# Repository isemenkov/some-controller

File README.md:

# some-controller

Some controller it is a test project to create simple input-output board with main power supply +24V.

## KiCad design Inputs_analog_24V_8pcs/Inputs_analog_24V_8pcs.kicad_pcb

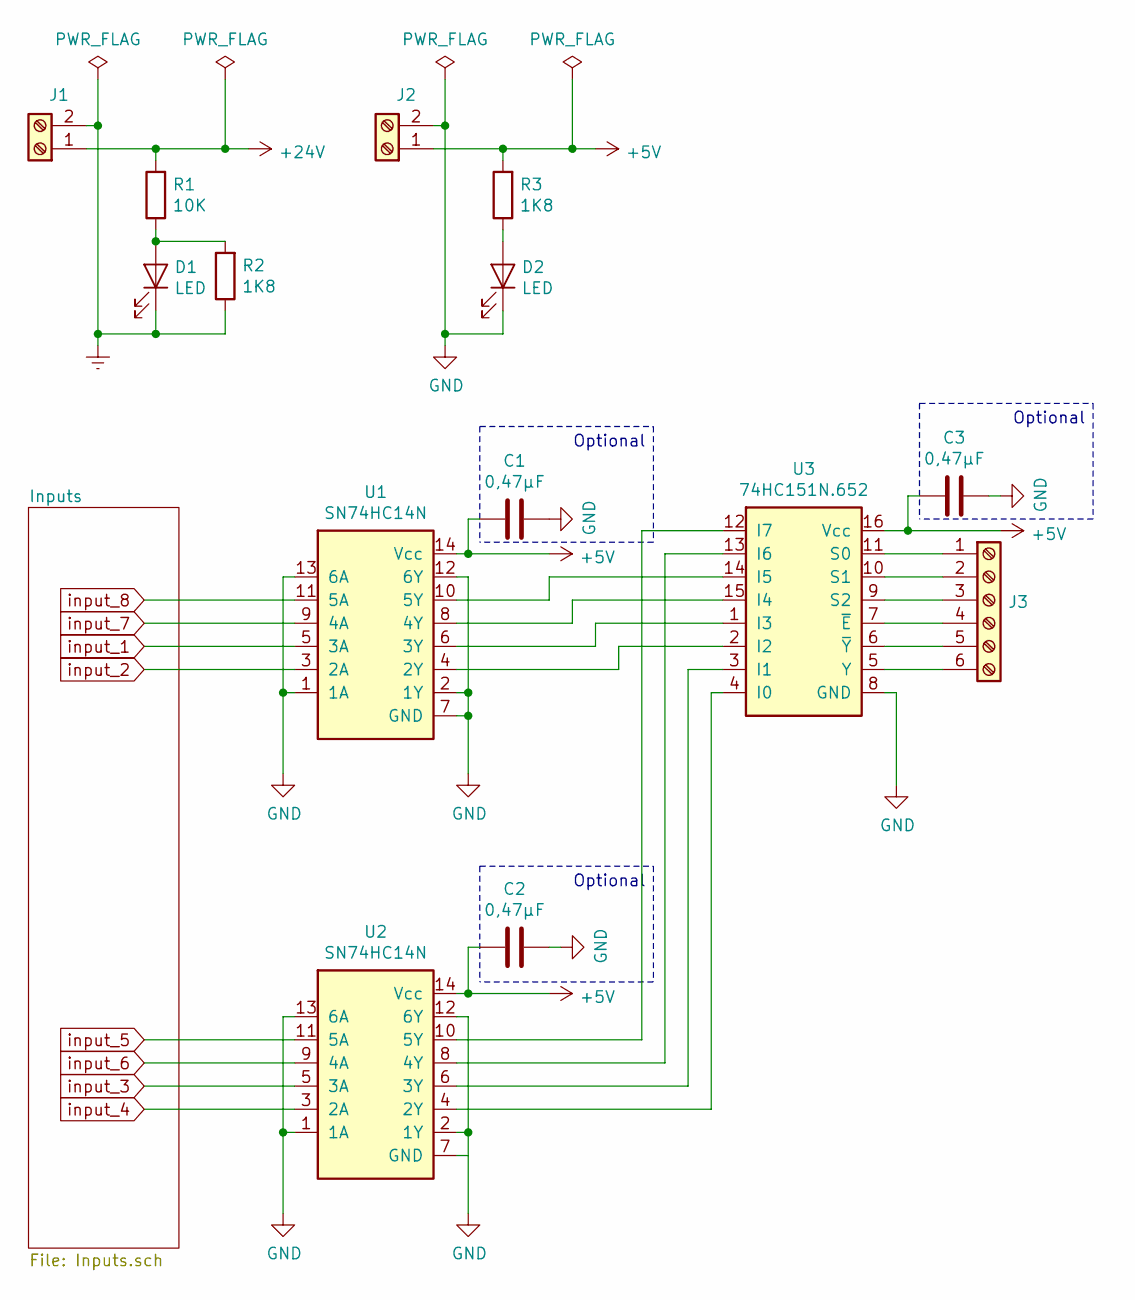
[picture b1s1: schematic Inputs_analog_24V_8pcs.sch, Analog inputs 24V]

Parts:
C1, C2, C3: 0,47μF; C_Disc_D4.3mm_W1.9mm_P5.00mm
D1, D2: LED; LED_D3.0mm
J1, J2: Screw_Terminal_01x02; TerminalBlock_MetzConnect_Type011_RT05502HBWC_1x02_P5.00mm_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
J3: Screw_Terminal_01x06; PinHeader_1x06_P2.54mm_Vertical
R1: 10K; R_Axial_DIN0207_L6.3mm_D2.5mm_P7.62mm_Horizontal
R2, R3: 1K8; R_Axial_DIN0207_L6.3mm_D2.5mm_P7.62mm_Horizontal
U1, U2: SN74HC14N; DIP-14_W7.62mm
U3: 74HC151N.652; DIP-16_W7.62mm

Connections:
+5V: C1.2, C2.2, C3.2, J2.1, R3.2, U1.14 (Vcc), U2.14 (Vcc), U3.16 (Vcc); also elsewhere on the board
+24V: J1.1, R1.2; also elsewhere on the board
Earth: D1.1 (K), J1.2, R2.1; also elsewhere on the board
GND: C1.1, C2.1, C3.1, D2.1 (K), J2.2, U1.1 (1A), U1.2 (1Y), U1.7 (GND), U1.12 (6Y), U1.13 (6A), U2.1 (1A), U2.2 (1Y), U2.7 (GND), U2.12 (6Y), U2.13 (6A), U3.8 (GND); also elsewhere on the board
unnamed: D1.2 (A), R1.1, R2.2
unnamed: D2.2 (A), R3.1
unnamed: J3.1, U3.11 (S0)
unnamed: J3.2, U3.10 (S1)
unnamed: J3.3, U3.9 (S2)
unnamed: J3.4, U3.7 (~E)
unnamed: J3.5, U3.6 (~Y)
unnamed: J3.6, U3.5 (Y)
unnamed: U1.4 (2Y), U3.2 (I2)
unnamed: U1.6 (3Y), U3.1 (I3)
unnamed: U1.8 (4Y), U3.15 (I4)
unnamed: U1.10 (5Y), U3.14 (I5)
unnamed: U2.4 (2Y), U3.4 (I0)
unnamed: U2.6 (3Y), U3.3 (I1)
unnamed: U2.8 (4Y), U3.13 (I6)
unnamed: U2.10 (5Y), U3.12 (I7)
input_1: U1.5 (3A); also elsewhere on the board
input_2: U1.3 (2A); also elsewhere on the board
input_3: U2.5 (3A); also elsewhere on the board
input_4: U2.3 (2A); also elsewhere on the board
input_5: U2.11 (5A); also elsewhere on the board
input_6: U2.9 (4A); also elsewhere on the board
input_7: U1.9 (4A); also elsewhere on the board
input_8: U1.11 (5A); also elsewhere on the board

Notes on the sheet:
Optional

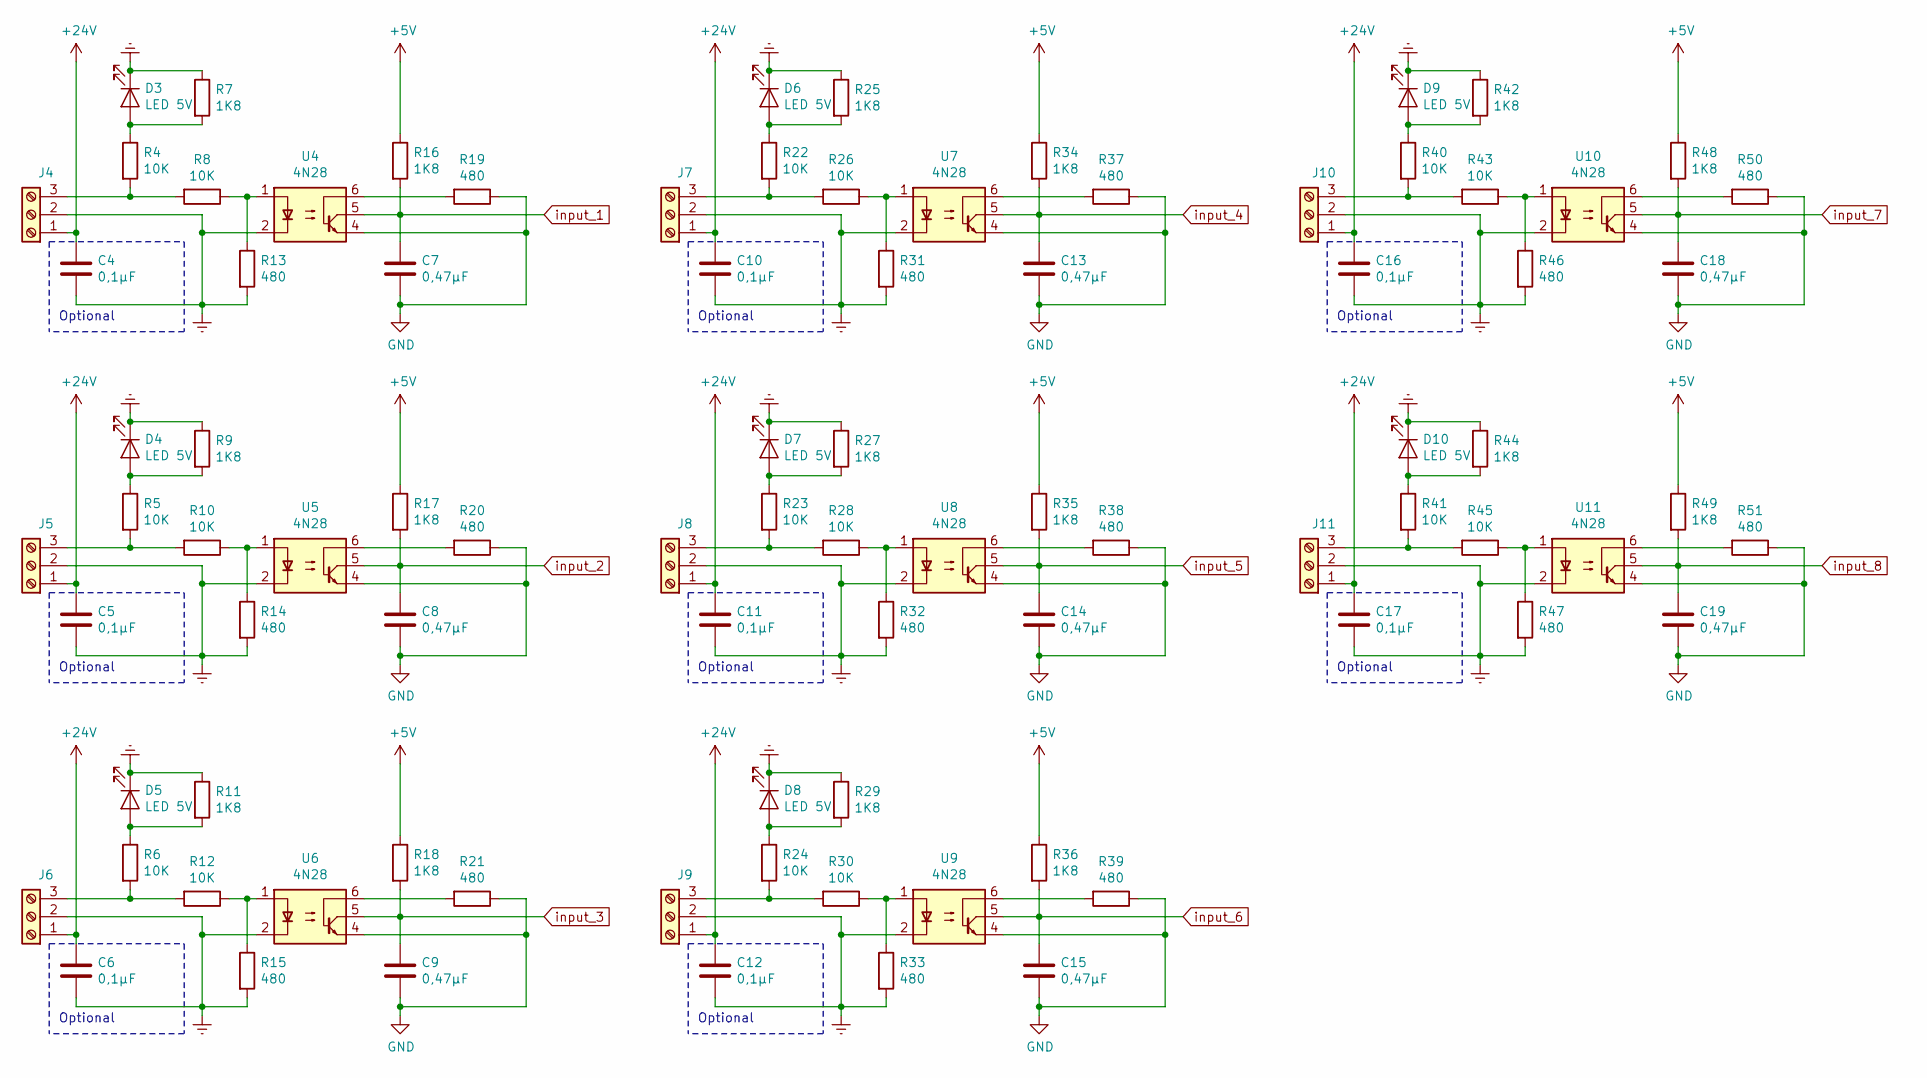
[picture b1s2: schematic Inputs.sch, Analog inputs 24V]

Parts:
C4, C5, C6, C10, C11, C12, C16, C17: 0,1μF; C_Disc_D4.3mm_W1.9mm_P5.00mm
C7, C8, C9, C13, C14, C15, C18, C19: 0,47μF; C_Disc_D4.3mm_W1.9mm_P5.00mm
D3, D4, D5, D6, D7, D8, D9, D10: LED 5V; LED_D3.0mm
J4: Screw_Terminal_01x03; TerminalBlock_MetzConnect_Type011_RT05503HBWC_1x03_P5.00mm_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
J5, J6, J7, J8, J9, J10, J11: Screw_Terminal_01x03; PinHeader_1x03_P2.54mm_Vertical
R4, R5, R6, R8, R10, R12, R22, R23, R24, R26, R28, R30, R40, R41, R43, R45: 10K; R_Axial_DIN0207_L6.3mm_D2.5mm_P7.62mm_Horizontal
R7, R9, R11, R16, R17, R18, R25, R27, R29, R34, R35, R36, R42, R44, R48, R49: 1K8; R_Axial_DIN0207_L6.3mm_D2.5mm_P7.62mm_Horizontal
R13, R14, R15, R19, R20, R21, R31, R32, R33, R37, R38, R39, R46, R47, R50, R51: 480; R_Axial_DIN0207_L6.3mm_D2.5mm_P7.62mm_Horizontal
U4, U5, U6, U7, U8, U9, U10, U11: 4N28; DIP-6_W7.62mm

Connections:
+5V: R16.1, R17.1, R18.1, R34.1, R35.1, R36.1, R48.1, R49.1; also elsewhere on the board
+24V: C4.1, C5.1, C6.1, C10.1, C11.1, C12.1, C16.1, C17.1, J4.1, J5.1, J6.1, J7.1, J8.1, J9.1, J10.1, J11.1; also elsewhere on the board
Earth: C4.2, C5.2, C6.2, C10.2, C11.2, C12.2, C16.2, C17.2, D3.1 (K), D4.1 (K), D5.1 (K), D6.1 (K), D7.1 (K), D8.1 (K), D9.1 (K), D10.1 (K), J4.2, J5.2, J6.2, J7.2, J8.2, J9.2, J10.2, J11.2, R7.1, R9.1, R11.1, R13.2, R14.2, R15.2, R25.1, R27.1, R29.1, R31.2, R32.2, R33.2, R42.1, R44.1, R46.2, R47.2, U4.2, U5.2, U6.2, U7.2, U8.2, U9.2, U10.2, U11.2; also elsewhere on the board
GND: C7.2, C8.2, C9.2, C13.2, C14.2, C15.2, C18.2, C19.2, R19.1, R20.1, R21.1, R37.1, R38.1, R39.1, R50.1, R51.1, U4.4, U5.4, U6.4, U7.4, U8.4, U9.4, U10.4, U11.4; also elsewhere on the board
unnamed: D3.2 (A), R4.1, R7.2
unnamed: D4.2 (A), R5.1, R9.2
unnamed: D5.2 (A), R6.1, R11.2
unnamed: D6.2 (A), R22.1, R25.2
unnamed: D7.2 (A), R23.1, R27.2
unnamed: D8.2 (A), R24.1, R29.2
unnamed: D9.2 (A), R40.1, R42.2
unnamed: D10.2 (A), R41.1, R44.2
unnamed: J4.3, R4.2, R8.2
unnamed: J5.3, R5.2, R10.2
unnamed: J6.3, R6.2, R12.2
unnamed: J7.3, R22.2, R26.2
unnamed: J8.3, R23.2, R28.2
unnamed: J9.3, R24.2, R30.2
unnamed: J10.3, R40.2, R43.2
unnamed: J11.3, R41.2, R45.2
unnamed: R10.1, R14.1, U5.1
unnamed: R12.1, R15.1, U6.1
unnamed: R8.1, R13.1, U4.1
unnamed: R19.2, U4.6
unnamed: R20.2, U5.6
unnamed: R21.2, U6.6
unnamed: R26.1, R31.1, U7.1
unnamed: R28.1, R32.1, U8.1
unnamed: R30.1, R33.1, U9.1
unnamed: R37.2, U7.6
unnamed: R38.2, U8.6
unnamed: R39.2, U9.6
unnamed: R43.1, R46.1, U10.1
unnamed: R45.1, R47.1, U11.1
unnamed: R50.2, U10.6
unnamed: R51.2, U11.6
input_1: C7.1, R16.2, U4.5; also elsewhere on the board
input_2: C8.1, R17.2, U5.5; also elsewhere on the board
input_3: C9.1, R18.2, U6.5; also elsewhere on the board
input_4: C13.1, R34.2, U7.5; also elsewhere on the board
input_5: C14.1, R35.2, U8.5; also elsewhere on the board
input_6: C15.1, R36.2, U9.5; also elsewhere on the board
input_7: C18.1, R48.2, U10.5; also elsewhere on the board
input_8: C19.1, R49.2, U11.5; also elsewhere on the board

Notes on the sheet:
Optional

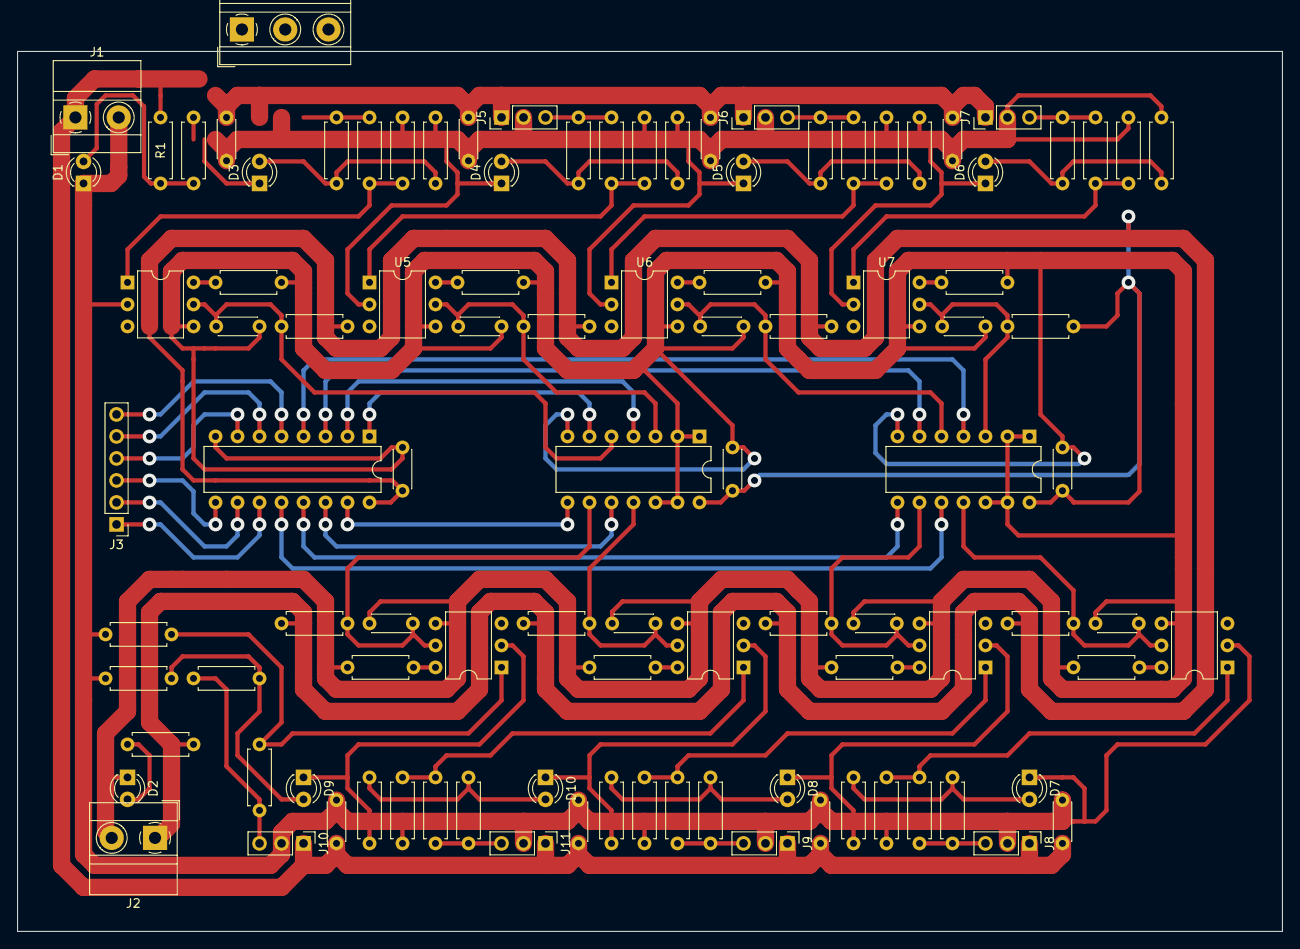
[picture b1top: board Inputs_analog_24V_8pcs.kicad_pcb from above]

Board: 2 copper layers, 146.1 x 101.6 mm, 102 parts (0 on the bottom side), 60 nets.

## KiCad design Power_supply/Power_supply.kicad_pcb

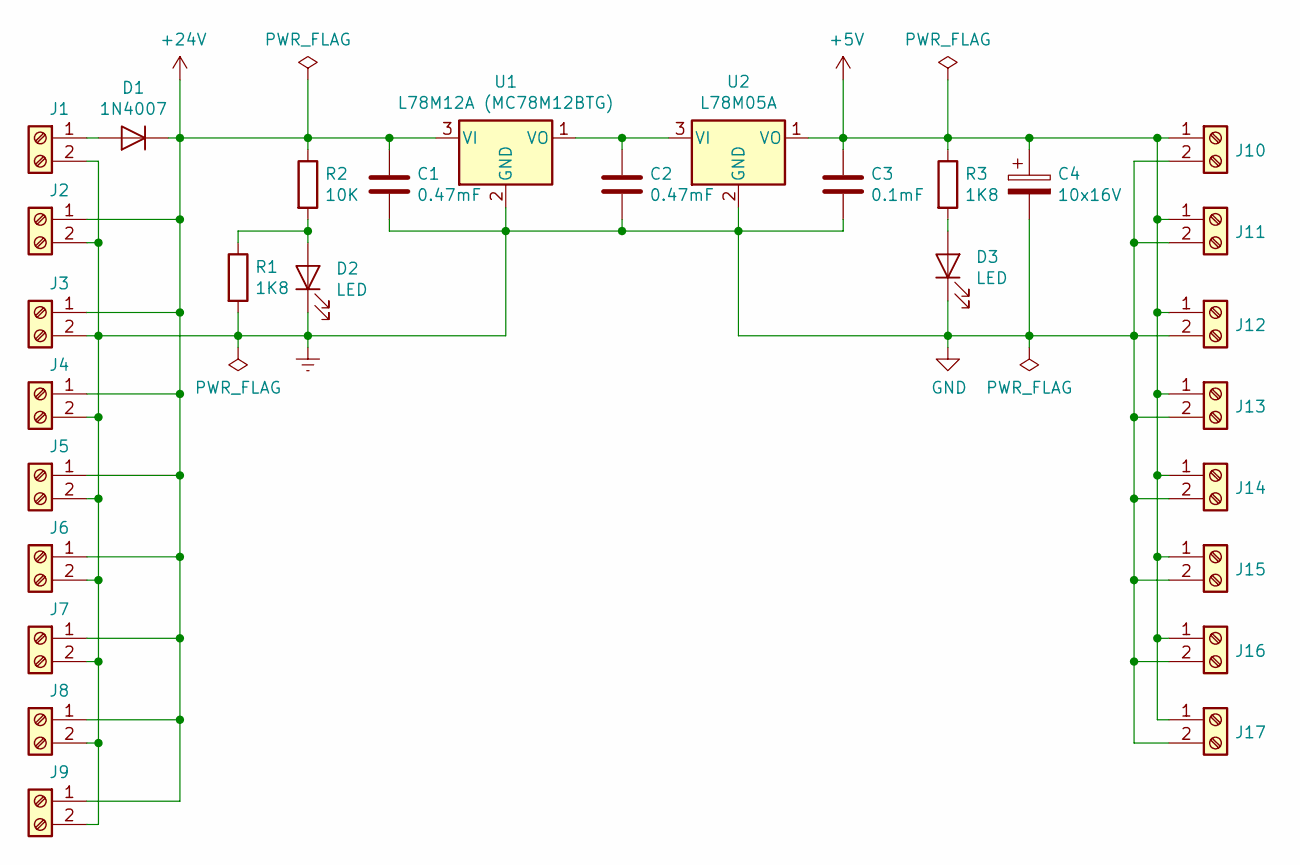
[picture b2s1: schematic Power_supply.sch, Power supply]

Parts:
C1, C2: 0.47mF; C_Disc_D4.3mm_W1.9mm_P5.00mm
C3: 0.1mF; C_Disc_D4.3mm_W1.9mm_P5.00mm
C4: 10x16V; CP_Radial_D8.0mm_P2.50mm
D1: 1N4007; D_A-405_P7.62mm_Horizontal
D2, D3: LED; LED_D5.0mm
J1, J2, J3, J4, J5, J6, J7, J8, J9, J10, J11, J12, J13, J14, J15, J16, J17: Screw_Terminal_01x02; PinHeader_1x02_P2.54mm_Vertical
R1, R3: 1K8; R_Axial_DIN0207_L6.3mm_D2.5mm_P7.62mm_Horizontal
R2: 10K; R_Axial_DIN0207_L6.3mm_D2.5mm_P7.62mm_Horizontal
U1: L78M12A (MC78M12BTG); TO-220-3_Vertical
U2: L78M05A; TO-220-3_Vertical

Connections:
+5V: C3.1, C4.1, J10.1, J11.1, J12.1, J13.1, J14.1, J15.1, J16.1, J17.1, R3.1, U2.1 (VO)
+24V: C1.1, D1.1 (K), J2.1, J3.1, J4.1, J5.1, J6.1, J7.1, J8.1, J9.1, R2.1, U1.3 (VI)
Earth: C1.2, C2.2, C3.2, C4.2, D2.1 (K), D3.1 (K), J1.2, J2.2, J3.2, J4.2, J5.2, J6.2, J7.2, J8.2, J9.2, J10.2, J11.2, J12.2, J13.2, J14.2, J15.2, J16.2, J17.2, R1.2, U1.2 (GND), U2.2 (GND)
unnamed: C2.1, U1.1 (VO), U2.3 (VI)
unnamed: D1.2 (A), J1.1
unnamed: D2.2 (A), R1.1, R2.2
unnamed: D3.2 (A), R3.2

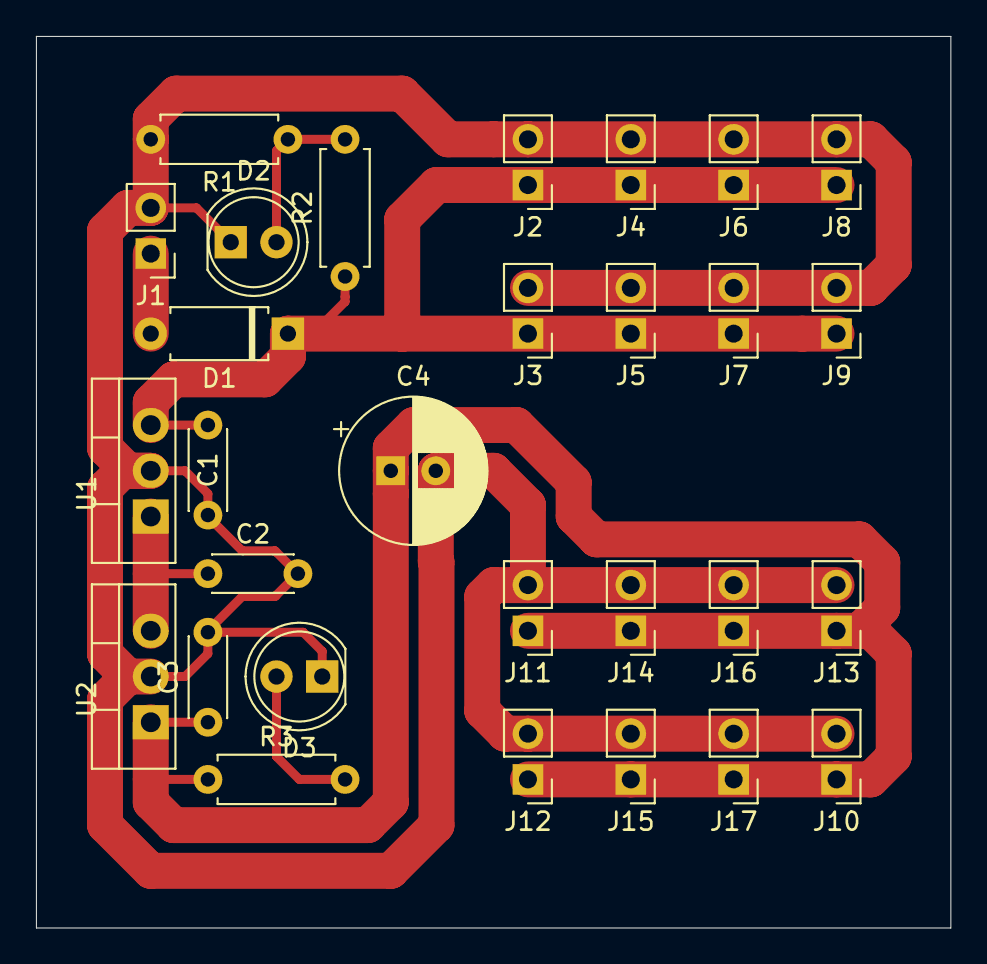
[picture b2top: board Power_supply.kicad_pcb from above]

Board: 2 copper layers, 50.8 x 49.5 mm, 29 parts (0 on the bottom side), 7 nets.

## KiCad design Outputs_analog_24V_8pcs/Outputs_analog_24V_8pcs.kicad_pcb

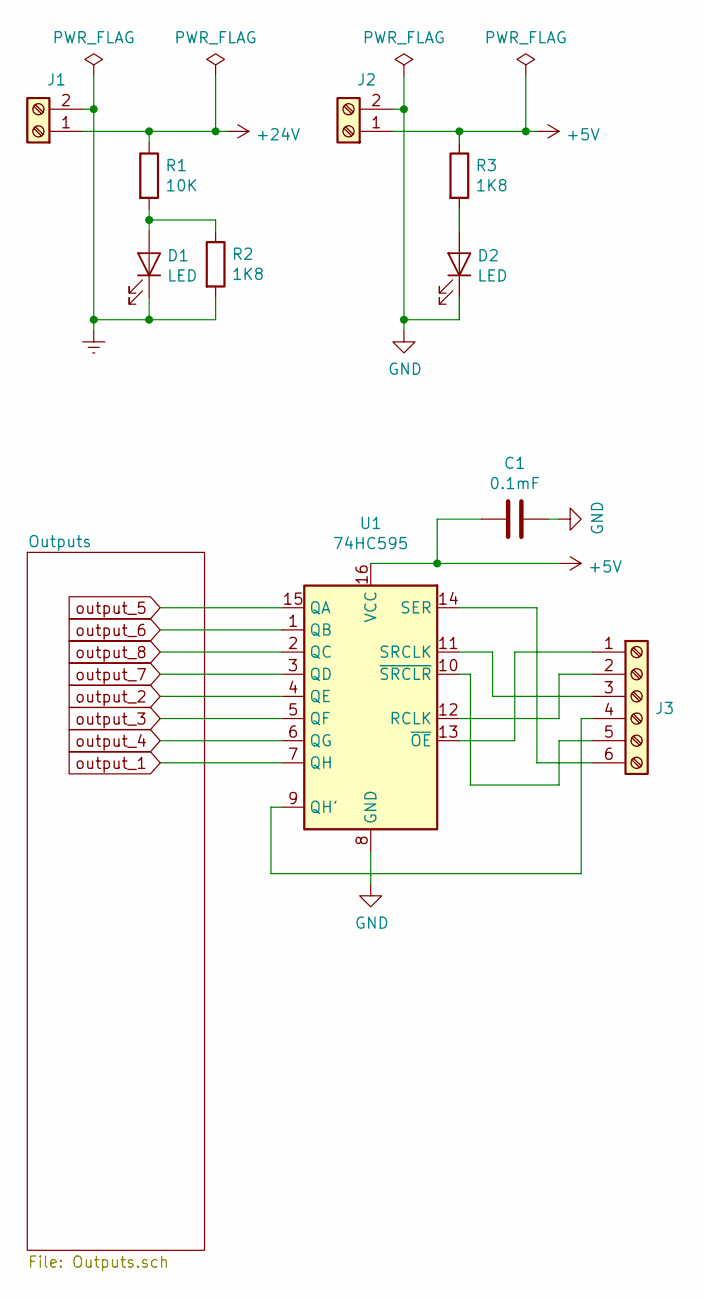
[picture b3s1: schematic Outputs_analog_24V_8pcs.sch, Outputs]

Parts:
C1: 0.1mF; C_Disc_D4.3mm_W1.9mm_P5.00mm
D1, D2: LED; LED_D3.0mm
J1, J2: Screw_Terminal_01x02; PinHeader_1x02_P2.54mm_Vertical
J3: Screw_Terminal_01x06; PinHeader_1x06_P2.54mm_Vertical
R1: 10K; R_Axial_DIN0207_L6.3mm_D2.5mm_P7.62mm_Horizontal
R2, R3: 1K8; R_Axial_DIN0207_L6.3mm_D2.5mm_P7.62mm_Horizontal
U1: 74HC595; DIP-16_W7.62mm

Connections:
+5V: C1.2, J2.1, R3.1, U1.16 (VCC)
+24V: J1.1, R1.1; also elsewhere on the board
Earth: D1.1 (K), J1.2, R2.2; also elsewhere on the board
GND: C1.1, D2.1 (K), J2.2, U1.8 (GND); also elsewhere on the board
unnamed: D1.2 (A), R1.2, R2.1
unnamed: D2.2 (A), R3.2
unnamed: J3.1, U1.13 (~OE)
unnamed: J3.2, U1.12 (RCLK)
unnamed: J3.3, U1.11 (SRCLK)
unnamed: J3.4, U1.9 (QH')
unnamed: J3.5, U1.10 (~SRCLR)
unnamed: J3.6, U1.14 (SER)
output_1: U1.7 (QH); also elsewhere on the board
output_2: U1.4 (QE); also elsewhere on the board
output_3: U1.5 (QF); also elsewhere on the board
output_4: U1.6 (QG); also elsewhere on the board
output_5: U1.15 (QA); also elsewhere on the board
output_6: U1.1 (QB); also elsewhere on the board
output_7: U1.3 (QD); also elsewhere on the board
output_8: U1.2 (QC); also elsewhere on the board

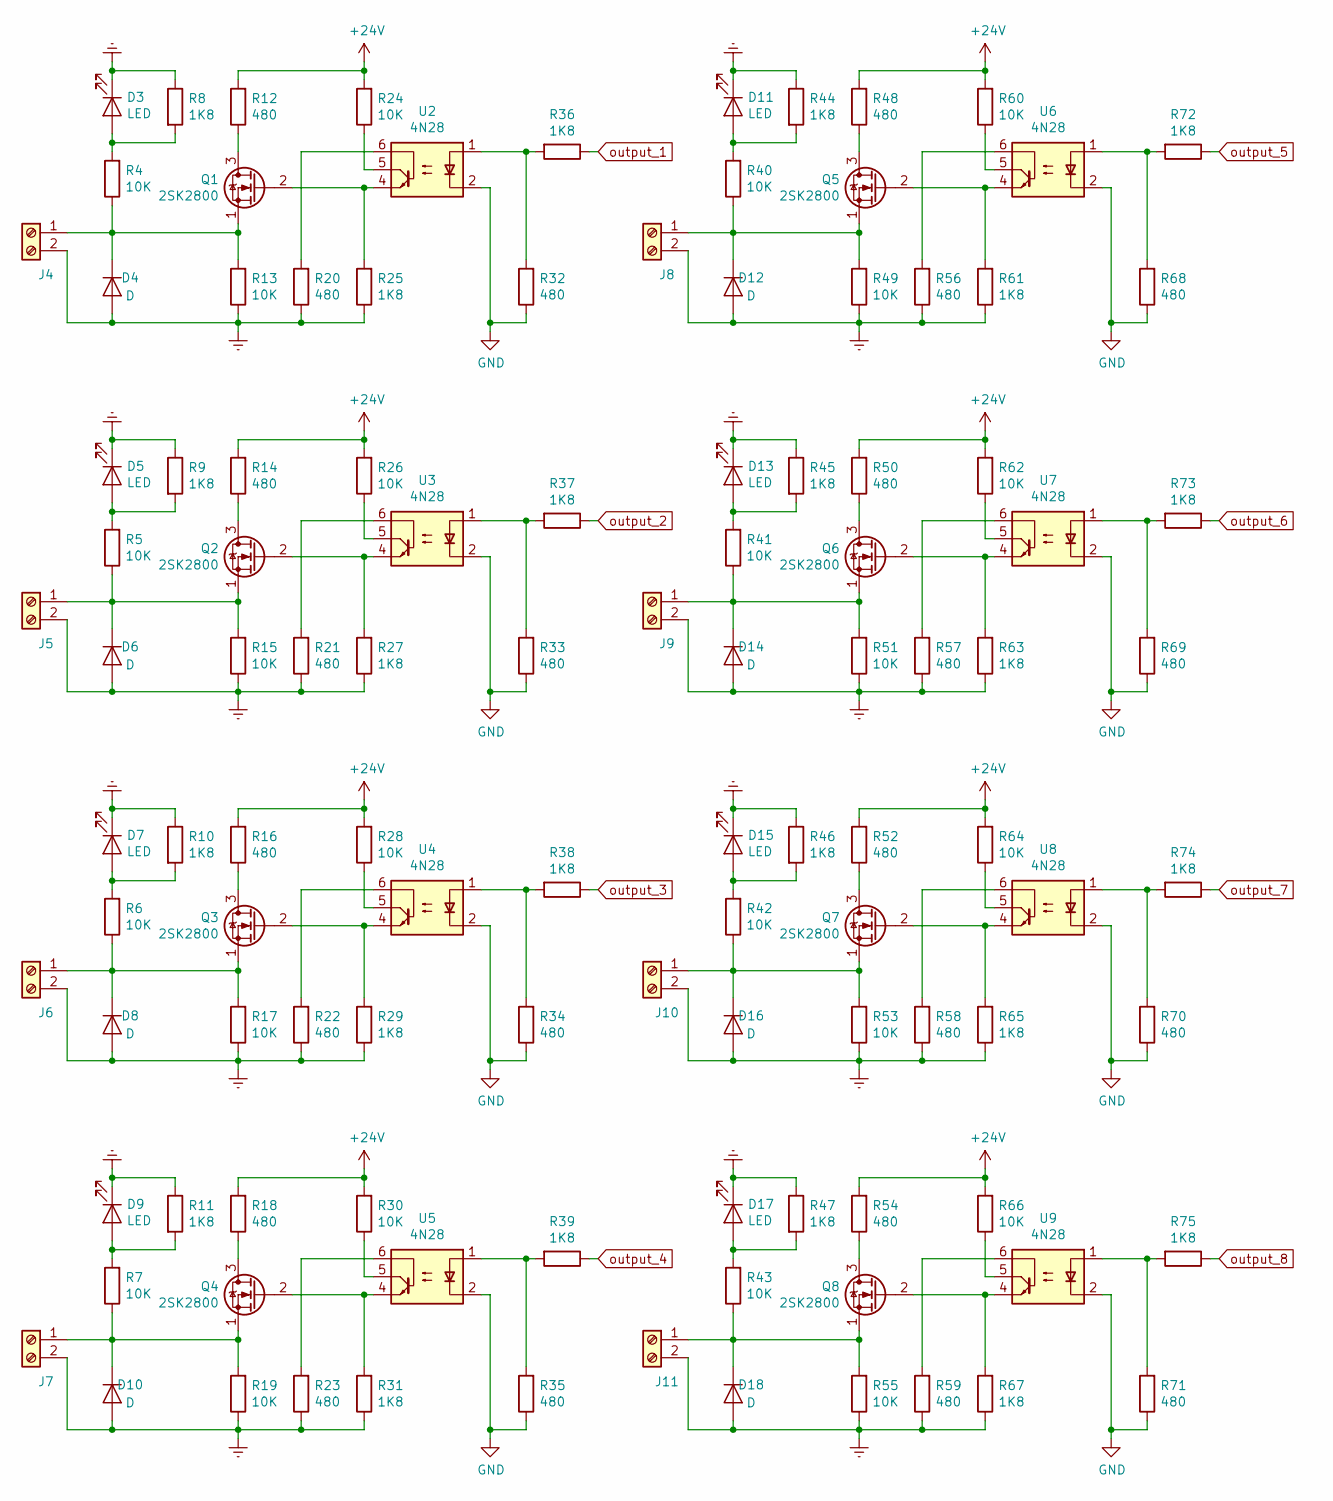
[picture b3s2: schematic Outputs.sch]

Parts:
D3, D5, D7, D9, D11, D13, D15, D17: LED; LED_D3.0mm
D4, D6, D8, D10, D12, D14, D16, D18: D; D_A-405_P7.62mm_Horizontal
J4, J5, J6, J7, J8, J9, J10, J11: Screw_Terminal_01x02; PinHeader_1x02_P2.54mm_Horizontal
Q1, Q2, Q3, Q4, Q5, Q6, Q7, Q8: 2SK2800; TO-220-3_Vertical
R4, R5, R6, R7, R13, R15, R17, R19, R24, R26, R28, R30, R40, R41, R42, R43, R49, R51, R53, R55, R60, R62, R64, R66: 10K; R_Axial_DIN0207_L6.3mm_D2.5mm_P7.62mm_Horizontal
R8, R9, R10, R11, R25, R27, R29, R31, R36, R37, R38, R39, R44, R45, R46, R47, R61, R63, R65, R67, R72, R73, R74, R75: 1K8; R_Axial_DIN0207_L6.3mm_D2.5mm_P7.62mm_Horizontal
R12, R14, R16, R18, R20, R21, R22, R23, R32, R33, R34, R35, R48, R50, R52, R54, R56, R57, R58, R59, R68, R69, R70, R71: 480; R_Axial_DIN0207_L6.3mm_D2.5mm_P7.62mm_Horizontal
U2, U3, U4, U5, U6, U7, U8, U9: 4N28; DIP-6_W7.62mm

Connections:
+24V: R12.2, R14.2, R16.2, R18.2, R24.2, R26.2, R28.2, R30.2, R48.2, R50.2, R52.2, R54.2, R60.2, R62.2, R64.2, R66.2; also elsewhere on the board
Earth: D3.1 (K), D4.2 (A), D5.1 (K), D6.2 (A), D7.1 (K), D8.2 (A), D9.1 (K), D10.2 (A), D11.1 (K), D12.2 (A), D13.1 (K), D14.2 (A), D15.1 (K), D16.2 (A), D17.1 (K), D18.2 (A), J4.2, J5.2, J6.2, J7.2, J8.2, J9.2, J10.2, J11.2, R8.1, R9.1, R10.1, R11.1, R13.1, R15.1, R17.1, R19.1, R20.1, R21.1, R22.1, R23.1, R25.1, R27.1, R29.1, R31.1, R44.1, R45.1, R46.1, R47.1, R49.1, R51.1, R53.1, R55.1, R56.1, R57.1, R58.1, R59.1, R61.1, R63.1, R65.1, R67.1; also elsewhere on the board
GND: R32.1, R33.1, R34.1, R35.1, R68.1, R69.1, R70.1, R71.1, U2.2, U3.2, U4.2, U5.2, U6.2, U7.2, U8.2, U9.2; also elsewhere on the board
unnamed: D3.2 (A), R4.2, R8.2
unnamed: D4.1 (K), J4.1, Q1.1 (S), R4.1, R13.2
unnamed: D5.2 (A), R5.2, R9.2
unnamed: D6.1 (K), J5.1, Q2.1 (S), R5.1, R15.2
unnamed: D7.2 (A), R6.2, R10.2
unnamed: D8.1 (K), J6.1, Q3.1 (S), R6.1, R17.2
unnamed: D9.2 (A), R7.2, R11.2
unnamed: D10.1 (K), J7.1, Q4.1 (S), R7.1, R19.2
unnamed: D11.2 (A), R40.2, R44.2
unnamed: D12.1 (K), J8.1, Q5.1 (S), R40.1, R49.2
unnamed: D13.2 (A), R41.2, R45.2
unnamed: D14.1 (K), J9.1, Q6.1 (S), R41.1, R51.2
unnamed: D15.2 (A), R42.2, R46.2
unnamed: D16.1 (K), J10.1, Q7.1 (S), R42.1, R53.2
unnamed: D17.2 (A), R43.2, R47.2
unnamed: D18.1 (K), J11.1, Q8.1 (S), R43.1, R55.2
unnamed: Q1.2 (G), R25.2, U2.4
unnamed: Q1.3 (D), R12.1
unnamed: Q2.2 (G), R27.2, U3.4
unnamed: Q2.3 (D), R14.1
unnamed: Q3.2 (G), R29.2, U4.4
unnamed: Q3.3 (D), R16.1
unnamed: Q4.2 (G), R31.2, U5.4
unnamed: Q4.3 (D), R18.1
unnamed: Q5.2 (G), R61.2, U6.4
unnamed: Q5.3 (D), R48.1
unnamed: Q6.2 (G), R63.2, U7.4
unnamed: Q6.3 (D), R50.1
unnamed: Q7.2 (G), R65.2, U8.4
unnamed: Q7.3 (D), R52.1
unnamed: Q8.2 (G), R67.2, U9.4
unnamed: Q8.3 (D), R54.1
unnamed: R20.2, U2.6
unnamed: R21.2, U3.6
unnamed: R22.2, U4.6
unnamed: R23.2, U5.6
unnamed: R24.1, U2.5
unnamed: R26.1, U3.5
unnamed: R28.1, U4.5
unnamed: R30.1, U5.5
unnamed: R32.2, R36.2, U2.1
unnamed: R33.2, R37.2, U3.1
unnamed: R34.2, R38.2, U4.1
unnamed: R35.2, R39.2, U5.1
unnamed: R56.2, U6.6
unnamed: R57.2, U7.6
unnamed: R58.2, U8.6
unnamed: R59.2, U9.6
unnamed: R60.1, U6.5
unnamed: R62.1, U7.5
unnamed: R64.1, U8.5
unnamed: R66.1, U9.5
unnamed: R68.2, R72.2, U6.1
unnamed: R69.2, R73.2, U7.1
unnamed: R70.2, R74.2, U8.1
unnamed: R71.2, R75.2, U9.1
output_1: R36.1; also elsewhere on the board
output_2: R37.1; also elsewhere on the board
output_3: R38.1; also elsewhere on the board
output_4: R39.1; also elsewhere on the board
output_5: R72.1; also elsewhere on the board
output_6: R73.1; also elsewhere on the board
output_7: R74.1; also elsewhere on the board
output_8: R75.1; also elsewhere on the board

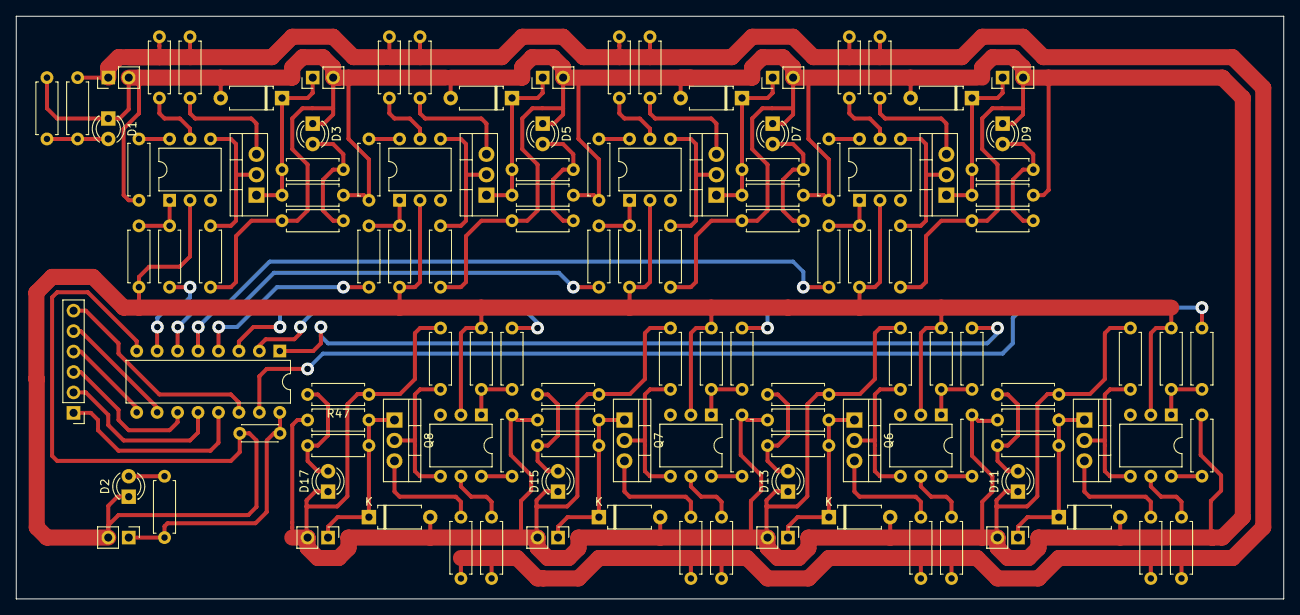
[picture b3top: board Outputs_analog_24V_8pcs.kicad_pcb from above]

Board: 2 copper layers, 157.5 x 72.4 mm, 122 parts (0 on the bottom side), 76 nets.

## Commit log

2020-03-20 Add inputs 8pcs 24V board
2020-03-20 Update pcb
2020-03-21 Finish pcb
2020-03-26 Update scmematics Add pcb second layer
2020-03-27 Redraw pcb
2020-03-27 Add outputs_24V_8pcs
2020-03-31 Update Inputs pcb
2020-03-31 Update Outputs pcb
2020-04-03 Update footprints
2020-04-03 Add power supply pcb
2020-04-07 Add Analog inputs 24V SMD pcb
2020-04-08 Change footprints for ternimals
